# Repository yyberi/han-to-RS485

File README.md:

# Aidon HAN to RS485 Adapter

A small PCB that reads data from the Aidon electricity meter's HAN port and converts it to an RS485 bus, enabling integration with home automation systems, data loggers, and industrial equipment.

**PCB size:** 45 × 25 mm, 4-layer  
**Designed:** November 2022 by Yyberi

---

## Background

Aidon smart electricity meters (used by many Nordic utilities) expose a **HAN port** — a standard RJ12 connector that outputs UART serial data (DLMS/COSEM P1 telegrams) at 115200 baud. This board taps into that port and re-transmits the data over RS485, which is suited for longer cable runs and multi-drop topologies.

---

## How It Works

```
Aidon meter
  HAN port (RJ12)
       │
       ├─ +5V ──────────────────── powers the board
       └─ TX (UART 115200 baud) ── NPN buffer (Q1) ──► MAX13487E ──► RS485 (A/B)
```

1. The meter provides 5 V on the HAN port — no external power supply needed.
2. The UART TX line from the meter is buffered through an NPN transistor (Q1) that also handles the logic-level inversion.
3. The MAX13487EESA+T RS485 transceiver with automatic direction control retransmits the data on the RS485 bus.
4. TVS diode (D3) protects the RS485 lines against ESD and transients.
5. Two LEDs indicate power (D2) and data transmission activity (D1).

---

## Connectors

| Ref | Connector | Function |
|-----|-----------|----------|
| J1  | RJ12 (DS1133-S60BPX) | HAN port — plugs into meter |
| J2  | 2-pin header 2.54 mm | Alternative/external power input (optional) |
| J3  | Phoenix Contact 3-pin 5.08 mm | RS485 output: A, B, GND |

### J1 — HAN Port Pinout (RJ12)

| Pin | Signal | Description |
|-----|--------|-------------|
| 1   | +5V    | Power from meter |
| 2   | –      | Not connected |
| 3   | DATA   | UART TX from meter (115200 8N1) |
| 4   | –      | Not connected |
| 5   | GND    | Ground |
| 6   | –      | Not connected |

### J3 — RS485 Output

| Pin | Signal | Board silkscreen (top→bottom) |
|-----|--------|-------------------------------|
| 1   | GND    | GND (bottom)                  |
| 2   | A (+)  | A (middle)                    |
| 3   | B (–)  | B (top)                       |

---

## Bill of Materials

| Ref | Value / Part | Package | LCSC # | Qty |
|-----|-------------|---------|--------|-----|
| IC1 | Maxim MAX13487EESA+T | SOIC-8 | C18347 | 1 |
| J1  | CONNFLY DS1133-S60BPX (RJ12) | Horizontal | C77859 | 1 |
| J2  | Molex 22284020 | 2×1 pin header 2.54 mm | C234182 | 1 |
| J3  | Phoenix Contact 1711738 | 3-pin 5.08 mm | C91156 | 1 |
| Q1  | MMS9013-H-TP (NPN) | SOT-23 | C90160 | 1 |
| D3  | ProTek PSM712-LF-T7 (TVS) | SOT-23 | C32677 | 1 |
| D1, D2 | NationStar NCD0805R1 (LED red) | 0805 | C84256 | 2 |
| R1, R3 | 510 Ω | 0805 | C17734 | 2 |
| R2  | 4.7 kΩ | 0805 | C17673 | 1 |
| R4  | 120 Ω (RS485 termination) | 0805 | C17437 | 1 |
| C1, C2 | 100 nF | 0805 | C49678 | 2 |

All LCSC part numbers are compatible with **JLCPCB SMT assembly**.

---

## Manufacturing

Gerber files, drill files, and pick-and-place position files are in the `AidonToRS485v2-gerbers/` folder.

### Ordering from JLCPCB

1. Zip the contents of `AidonToRS485v2-gerbers/`.
2. Upload to [jlcpcb.com](https://jlcpcb.com) and select **4 layers**.
3. For SMT assembly, upload the BOM (`BOM_AidonToRS485v2.xlsx`) and the position files (`*-top-pos.csv`).

**Recommended PCB stackup:** standard JLC04161H-7628 (or equivalent).

---

## Data Format

The Aidon meter outputs **DLMS/COSEM** P1 telegrams (similar to DSMR P1). Data is sent as UART at **115200 baud, 8N1** (8 data bits, no parity, 1 stop bit).

Library for parsing Aidon data:
- [aidon-comm](https://github.com/yyberi/aidon-comm) - HAN serial data to MQTT

---

## Getting Started

1. **Plug** the RJ12 cable into the meter's HAN port and the board's J1.
2. **Connect** your RS485 device or bus to J3 (A, B, GND).
3. **Power** is sourced directly from the meter. No external supply needed.
4. Configure your RS485 receiver for **115200 baud, 8N1**.
5. Data telegrams arrive automatically — the meter pushes data every 10 seconds (or as configured by the utility).

> **Note:** Some utilities require you to request HAN port activation from your grid operator before data is available.

---

## Repository Contents

```
AidonToRS485_v2/
├── AidonToRS485.kicad_pro       # KiCad project file
├── AidonToRS485.kicad_sch       # Schematic
├── AidonToRS485.kicad_pcb       # PCB layout
├── AidonToRS485.step            # 3D model (STEP)
├── BOM_AidonToRS485v2.xlsx      # Bill of materials (JLCPCB format)
├── BOM_AidonToRS485.csv         # Bill of materials (CSV)
└── AidonToRS485v2-gerbers/      # Gerber + drill + position files
```

---

## License

This hardware design is released under the **CERN Open Hardware Licence v2 – Permissive (CERN-OHL-P)**. You are free to use, modify, and manufacture this design, with or without attribution, and without requiring derivatives to be open source.

See [ohwr.org/cern_ohl_p_v2.txt](https://ohwr.org/cern_ohl_p_v2.txt) for the full license text.

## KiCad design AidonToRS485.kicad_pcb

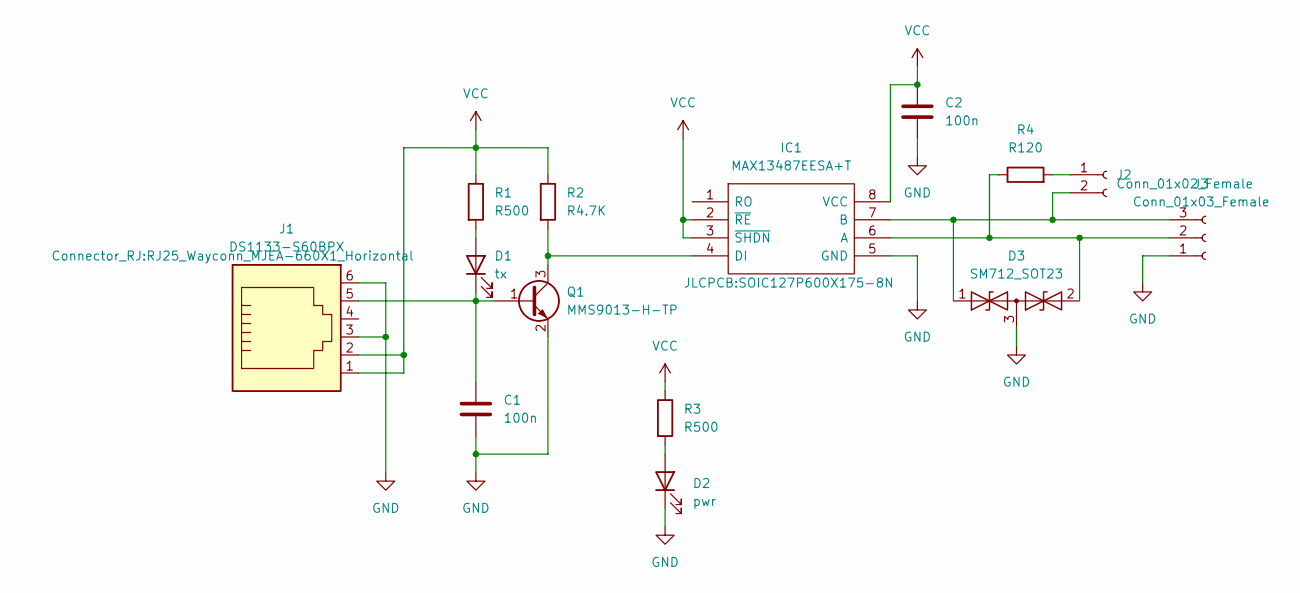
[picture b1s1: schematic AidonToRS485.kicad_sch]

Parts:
C1, C2: 100n; C_0805_2012Metric
D1: tx; LED_0805_2012Metric; JLCPCB Part # C84256
D2: pwr; LED_0805_2012Metric; JLCPCB Part # C84256
D3: SM712_SOT23; SOT-23; JLCPCB Part # C404012
IC1: MAX13487EESA+T; SOIC127P600X175-8N; Manufacturer_Part_Number MAX13487EESA+T; Mouser Part Number 700-MAX13487EESAT
J1: DS1133-S60BPX; RJ25_Wayconn_MJEA-660X1_Horizontal; JLCPCB Part # C77859
J2: Conn_01x02_Female; PinHeader_2x01_P2.54mm_Vertical; JLCPCB Part # C234182
J3: Conn_01x03_Female; TerminalBlock_Phoenix_MKDS-1,5-3-5.08_1x03_P5.08mm_Horizont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; JLCPCB Part # C91156
Q1: MMS9013-H-TP; SOT-23; JLCPCB Part # C90160
R1, R3: R500; R_0805_2012Metric
R2: R4.7K; R_0805_2012Metric
R4: R120; R_0805_2012Metric

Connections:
GND: C1.2, C2.2, D2.1 (K), D3.3 (common), IC1.5 (GND), J1.3, J1.6, J3.1, Q1.2 (E)
unnamed: C1.1, D1.1 (K), J1.5, Q1.1 (B)
unnamed: D1.2 (A), R1.2
unnamed: D2.2 (A), R3.2
unnamed: D3.1 (A1), IC1.7 (B), J2.2, J3.3
unnamed: D3.2 (A2), IC1.6 (A), J3.2, R4.1
unnamed: IC1.4 (DI), Q1.3 (C), R2.2
unnamed: J2.1, R4.2
VCC: C2.1, IC1.2 (~RE), IC1.3 (~SHDN), IC1.8 (VCC), J1.1, J1.2, R1.1, R2.1, R3.1

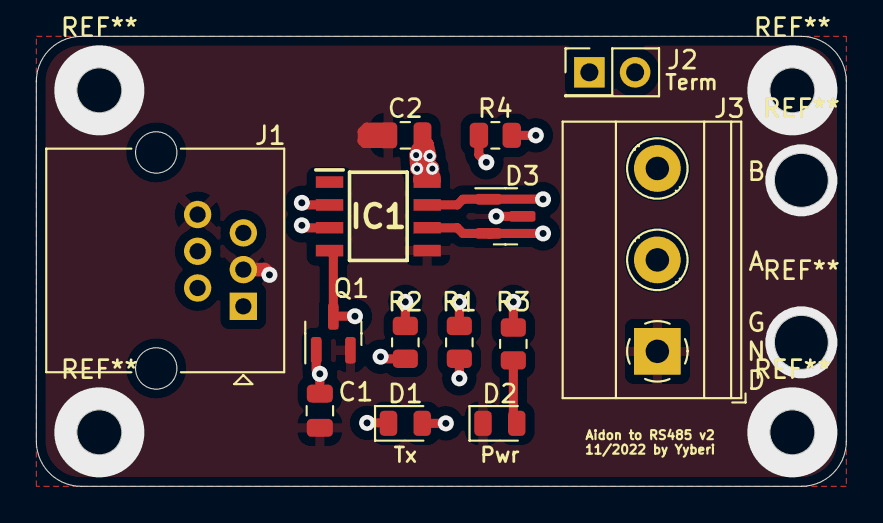
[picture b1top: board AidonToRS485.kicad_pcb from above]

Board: 4 copper layers, 45.0 x 25.0 mm, 14 parts (0 on the bottom side), 9 nets.

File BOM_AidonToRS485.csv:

Comment;Designator;Footprint;LCSC Part Number;Quantity
120R;R4;0805;C17909;1
510R;R3,R1;0805;C17734;2
4K7;R2;0805;C17673;1
MMS9013-H-TP;Q1;SOT-23;C90160;1
Phoenix Contact 1711738;J3;Phoenix_MKDS-1.5-3-5.08_1x03_P5.08mm_Horizontal;C91156;1
MOLEX 22284020;J2;PinHeader_2x01_P2.54mm_Vertical;C234182;1
CONNFLY Elec DS1133-S60BPX;J1;DS1133-S60BPX;C77859;1
Maxim Integrated MAX13487EESA+T;IC1;SOIC-8_150mil;C18347;1
BOURNS CDSOT23-SM712;D3;SOT-23;C404012;1
Foshan NationStar Optoelectronics NCD0805R1;D2;0805;C84256;1
Foshan NationStar Optoelectronics NCD0805R1;D1;0805;C84256;1
100nF;C2,C1;0805;C49678;2

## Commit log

2026-06-07 Fix: J3 pins
2026-06-07 Doc: Aidon han manual
2026-06-09 Doc: update link to commication library
